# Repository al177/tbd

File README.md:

# tbd
Tiny Bit Dingus

A really tiny, really simple ARM USB thing.  More project details at hackaday.io: http://hackaday.io/project/4826-tiny-bit-dingus

v0.1 manufacturing files are in the v0.1 branch

Thanks to Sparkfun for their component library.

This work is licensed under the Creative Commons Attribution-ShareAlike 4.0 International License. To view a copy of this license, visit http://creativecommons.org/licenses/by-sa/4.0/ or send a letter to Creative Commons, PO Box 1866, Mountain View, CA 94042, USA.

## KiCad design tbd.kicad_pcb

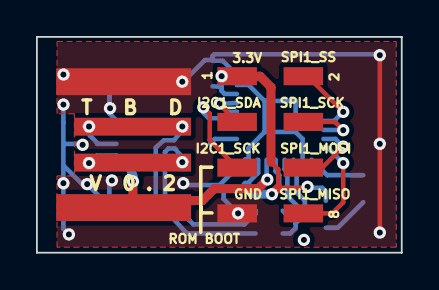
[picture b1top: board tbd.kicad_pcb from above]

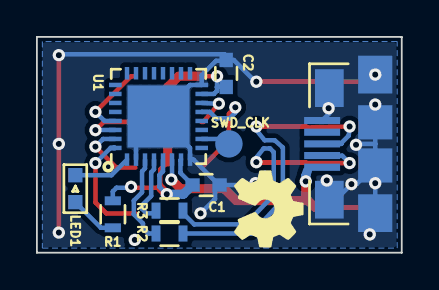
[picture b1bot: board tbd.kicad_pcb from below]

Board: 2 copper layers, 20.3 x 12.0 mm, 11 parts (9 on the bottom side), 16 nets.

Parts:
C1, C2: 100nF; C_0603
J1: USBPCB; tbd_USB_A_PCB
J2: USB-MICROB-5PIN; SparkFun-USB-MICROB
LED1: LED0603; LED-0603
P1: CONN_02X04; HEADER_2x4_SMT_RA
R1: 100R; R_0603
R2, R3: 33R; R_0603
SWD_CLK: SWD_CLK; Measurement_Point_Round-SMD-Pad_Small
U1: MKL27ZxxxVFM4; QFN-32-1EP_5x5mm_Pitch0.5mm

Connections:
+3.3V: C1.1, C2.1, P1.1, R1.1, U1.5, U1.7, U1.15
I2C1_SCL: P1.5, U1.13
I2C1_SDA: P1.3, U1.14
unnamed: J1.5V, J2.VBUS, U1.6
unnamed: J1.DN, J2.D-, R3.1
unnamed: J1.DP, J2.D+, R2.1
unnamed: LED1.A, R1.2
unnamed: LED1.C, U1.1
unnamed: R2.2, U1.3
unnamed: R3.2, U1.4
unnamed: SWD_CLK.1, U1.10
SPI1_MISO: P1.8, U1.32
SPI1_MOSI: P1.6, U1.31
SPI1_SCK: P1.4, U1.30
SPI1_SS: P1.2, U1.29
VSS: C1.2, C2.2, J1.GND, J2.GND, J2.MTN1, J2.MTN2, J2.MTN3, J2.MTN4, J2.MTN5, J2.MTN6, P1.7, U1.2, U1.8, U1.16, U1.33

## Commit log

2015-04-04 Initial commit tbdv0.1 RTP
2015-04-04 Add CC-BY-SA 4.0 text license
2015-04-15 Clean up unneeded files, remove v0.1 RTP files since they're in the v0.1 branch
2015-06-17 Add OSHW logo, clean up silk
2015-06-17 Stitch ground plane near USB resistors, hackaday.io URL as board ID, add port IDs to pins and LED
2015-06-17 Add production files for v0.2
